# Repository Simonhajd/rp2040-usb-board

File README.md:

# RP2040 USB Board (12×38mm)

A minimal RP2040 USB device board designed to fit within a 12mm × 38mm footprint, which is roughly the size of a small USB drive.

This project started from an RP2040 reference design and was stripped down to only the systems required for the USB device operation. I changed the flash and power components and entirely redesigned the layout to meet the width constraint, which matches the width of a standard USB port.

---

## What’s On It

* RP2040 (QFN)
* External QSPI flash
* 3.3V regulator
* Native USB interface
* Single status LED
* 2-layer PCB

There's no GPIO breakout since I intended to make a compact reliable RP2040 rather than a development board.

---

## Why

I wanted to see how small a functional RP2040 implementation could reasonably be made while still following the datasheet requirements.

The goal wasn’t to create a dev board, but a compact usb device.

---

## Status

Rev A boards are currently in fabrication and will be tested upon arrival.

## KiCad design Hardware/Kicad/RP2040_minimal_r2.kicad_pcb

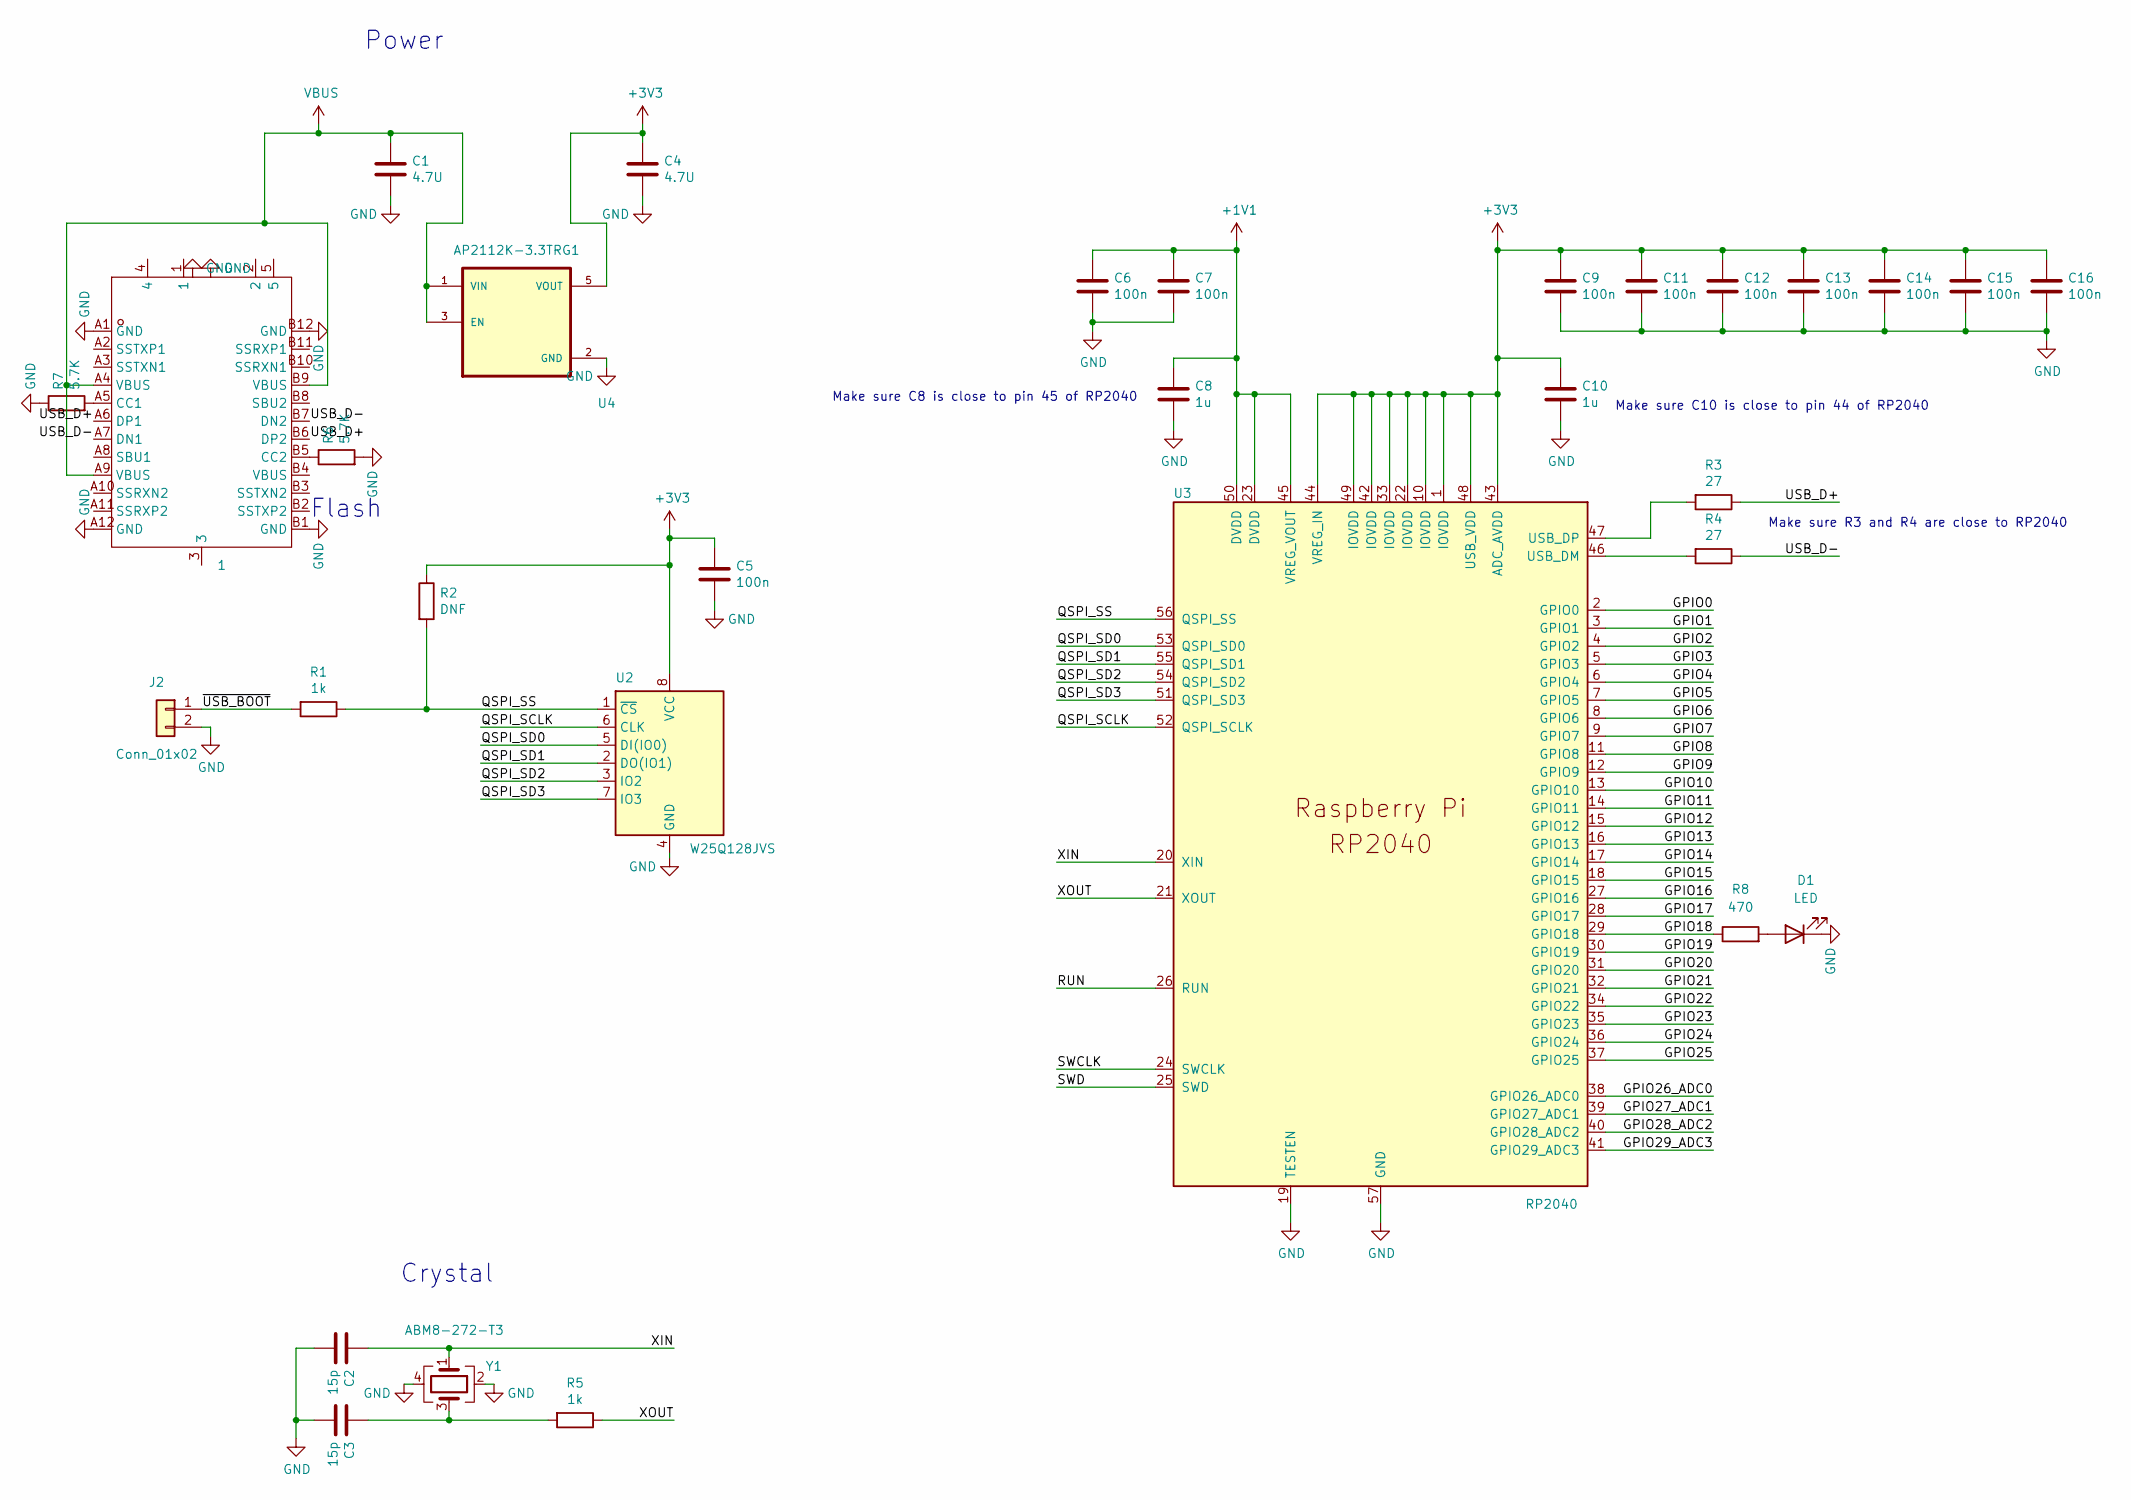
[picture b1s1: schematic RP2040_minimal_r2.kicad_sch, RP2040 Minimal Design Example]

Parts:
1: (no value)
C1, C4: 4.7U; C_0402_1005Metric
C2, C3: 15p; C_0402_1005Metric
C5, C6, C7, C9, C11, C12, C13, C14, C15, C16: 100n; C_0402_1005Metric
C8, C10: 1u; C_0402_1005Metric
D1: LED; LED_0603_1608Metric
J2: Conn_01x02; PinHeader_1x02_P2.54mm_Vertical
R1, R5: 1k; R_0402_1005Metric
R2: DNF; R_0402_1005Metric
R3, R4: 27; R_0402_1005Metric
R6, R7: 5.7K; R_0402_1005Metric
R8: 470; C_0402_1005Metric
U2: W25Q128JVS; Winbond_USON-8-1EP_3x2mm_P0.5mm_EP0.2x1.6mm
U3: RP2040; RP2040-QFN-56
U4: AP2112K-3.3TRG1; SOT95P285X140-5N; PARTREV 2-2
Y1: ABM8-272-T3; Crystal_SMD_3225-4Pin_3.2x2.5mm

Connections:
+1V1: C6.1, C7.1, C8.1, U3.23 (DVDD), U3.45 (VREG_VOUT), U3.50 (DVDD)
+3V3: C4.1, C5.1, C9.1, C10.1, C11.1, C12.1, C13.1, C14.1, C15.1, C16.1, R2.1, U2.8 (VCC), U3.1 (IOVDD), U3.10 (IOVDD), U3.22 (IOVDD), U3.33 (IOVDD), U3.42 (IOVDD), U3.43 (ADC_AVDD), U3.44 (VREG_IN), U3.48 (USB_VDD), U3.49 (IOVDD), U4.5 (VOUT)
/GPIO0: U3.2 (GPIO0)
/GPIO1: U3.3 (GPIO1)
/GPIO2: U3.4 (GPIO2)
/GPIO3: U3.5 (GPIO3)
/GPIO4: U3.6 (GPIO4)
/GPIO5: U3.7 (GPIO5)
/GPIO6: U3.8 (GPIO6)
/GPIO7: U3.9 (GPIO7)
/GPIO8: U3.11 (GPIO8)
/GPIO9: U3.12 (GPIO9)
/GPIO10: U3.13 (GPIO10)
/GPIO11: U3.14 (GPIO11)
/GPIO12: U3.15 (GPIO12)
/GPIO13: U3.16 (GPIO13)
/GPIO14: U3.17 (GPIO14)
/GPIO15: U3.18 (GPIO15)
/GPIO16: U3.27 (GPIO16)
/GPIO17: U3.28 (GPIO17)
/GPIO18: R8.1, U3.29 (GPIO18)
/GPIO19: U3.30 (GPIO19)
/GPIO20: U3.31 (GPIO20)
/GPIO21: U3.32 (GPIO21)
/GPIO22: U3.34 (GPIO22)
/GPIO23: U3.35 (GPIO23)
/GPIO24: U3.36 (GPIO24)
/GPIO25: U3.37 (GPIO25)
/GPIO26_ADC0: U3.38 (GPIO26_ADC0)
/GPIO27_ADC1: U3.39 (GPIO27_ADC1)
/GPIO28_ADC2: U3.40 (GPIO28_ADC2)
/GPIO29_ADC3: U3.41 (GPIO29_ADC3)
/QSPI_SCLK: U2.6 (CLK), U3.52 (QSPI_SCLK)
/QSPI_SD0: U2.5 (DI(IO0)), U3.53 (QSPI_SD0)
/QSPI_SD1: U2.2 (DO(IO1)), U3.55 (QSPI_SD1)
/QSPI_SD2: U2.3 (IO2), U3.54 (QSPI_SD2)
/QSPI_SD3: U2.7 (IO3), U3.51 (QSPI_SD3)
/QSPI_SS: R1.1, R2.2, U2.1 (~CS), U3.56 (QSPI_SS)
/RUN: U3.26 (RUN)
/SWCLK: U3.24 (SWCLK)
/SWD: U3.25 (SWD)
/USB_D+: 1.A6 (DP1), 1.B6 (DP2), R3.1
/USB_D-: 1.A7 (DN1), 1.B7 (DN2), R4.1
/XIN: C2.1, U3.20 (XIN), Y1.1
/XOUT: R5.1, U3.21 (XOUT)
GND: 1.A1 (GND), 1.A12 (GND), 1.B1 (GND), 1.B12 (GND), C1.2, C2.2, C3.2, C4.2, C5.2, C6.2, C7.2, C8.2, C9.2, C10.2, C11.2, C12.2, C13.2, C14.2, C15.2, C16.2, D1.1 (K), J2.2, R6.2, R7.1, U2.4 (GND), U3.19 (TESTEN), U3.57 (GND), U4.2 (GND), Y1.2, Y1.4
unnamed: 1.A5 (CC1), R7.2
unnamed: 1.B5 (CC2), R6.1
unnamed: C3.1, R5.2, Y1.3
unnamed: D1.2 (A), R8.2
unnamed: J2.1, R1.2
unnamed: R4.2, U3.46 (USB_DM)
unnamed: R3.2, U3.47 (USB_DP)
VBUS: 1.A4 (VBUS), 1.A9 (VBUS), 1.B9 (VBUS), C1.1, U4.1 (VIN), U4.3 (EN)

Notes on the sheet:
Power
Crystal
Make sure C8 is close to pin 45 of RP2040
Make sure C10 is close to pin 44 of RP2040
Make sure R3 and R4 are close to RP2040
Flash

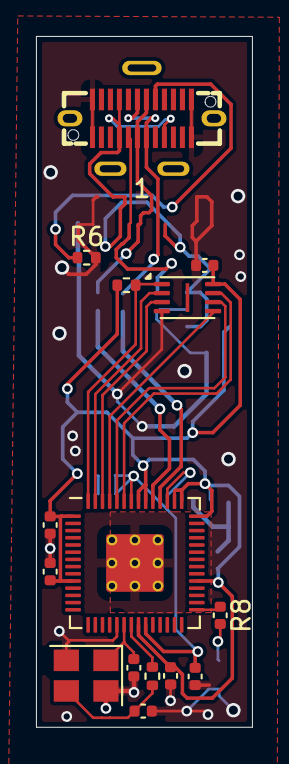
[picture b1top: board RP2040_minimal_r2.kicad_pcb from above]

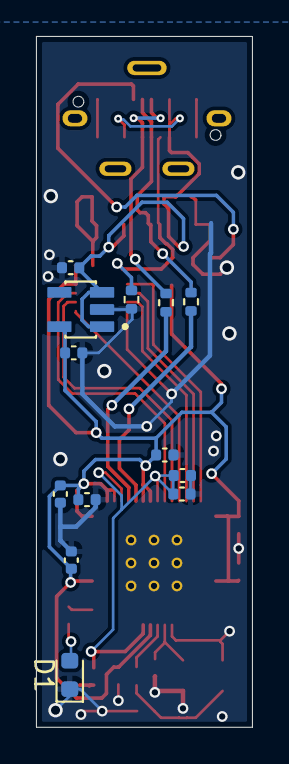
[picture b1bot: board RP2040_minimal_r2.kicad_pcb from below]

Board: 2 copper layers, 12.0 x 38.4 mm, 28 parts (13 on the bottom side), 21 nets.

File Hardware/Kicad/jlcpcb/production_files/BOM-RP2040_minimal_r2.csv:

Comment,Designator,Footprint,LCSC,Quantity
1u,C10,C_0402_1005Metric,,1
27,R4,R_0402_1005Metric,,1
100n,C6,C_0402_1005Metric,,1
100n,C12,C_0402_1005Metric,,1
100n,C9,C_0402_1005Metric,,1
27,R3,R_0402_1005Metric,,1
5.7K,R7,R_0402_1005Metric,,1
AP2112K-3.3TRG1,U4,SOT95P285X140-5N,,1
4.7U,C1,C_0402_1005Metric,,1
4.7U,C4,C_0402_1005Metric,,1
1u,C8,C_0402_1005Metric,,1
100n,C15,C_0402_1005Metric,,1
5.7K,R6,R_0402_1005Metric,,1
100n,C7,C_0402_1005Metric,,1
ABM8-272-T3,Y1,Crystal_SMD_3225-4Pin_3.2x2.5mm,,1
100n,C5,C_0402_1005Metric,,1
W25Q128JVS,U2,Winbond_USON-8-1EP_3x2mm_P0.5mm_EP0.2x1.6mm,,1
RP2040,U3,RP2040-QFN-56,,1
100n,C14,C_0402_1005Metric,,1
100n,C11,C_0402_1005Metric,,1
1k,R5,R_0402_1005Metric,,1
DNF,R2,R_0402_1005Metric,,1
15p,C3,C_0402_1005Metric,,1
15p,C2,C_0402_1005Metric,,1
100n,C13,C_0402_1005Metric,,1
~,1,USB-C-SMD_TYPE-C-31-G-09,,1
470,R8,C_0402_1005Metric,,1
LED,D1,LED_0603_1608Metric,,1

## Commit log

2026-02-16 reorg
